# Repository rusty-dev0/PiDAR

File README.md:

# PiDAR
An autonomous robot that builds a real-time 2D map of an unknown room using LiDAR and SLAM, with live visualization and path tracking, and even a custom development board for all of its locomotive needs!

### Programming stuff:

The majority of the code here written for the kineticBoard would be written in the Pico C SDK. This is because abstraction, as seen with MicroPython, often causes delays and doesn't provide full control over the hardware. The Pi would be programmed in Python because it is better for data processing, visualizations, and (potentially) machine learning algorithms.

### A Little Context
I've always wanted to learn more about LiDARs and autonomous vehicles. This project will also serve as one of my projects for the online portion of the *Stasis* Hackathon, a Hack Club event.

## Organization and Flow
This project is basically divided into a few tiny subproblems that each component is designed to tackle. 
1) The LiDAR (at the top) is meant to collect data by sweeping the polar grid and recording ToF data when obstacles are detected (it knows this because its signal would bounce back). The LiDAR then feeds this real-time data to a Raspberry Pi 4 Model B.
2) The Pi, on the layer below, processes the data and allows for stuff like visualizations and algorithms. It's basically the brain of the robot. It takes an input from the layer above, processes it, and then handles an appropriate response such as sending a signal to the kineticBoard or responding to a request on its webserver.
3) The kineticBoard, at the very bottom, connects to the +12V LiPo and handles all of the low-level stuff with the motors. It connects to the encoders and reads the pulses generated by its fluctuating magnetic field, and also drives a response from its built-in TB6612FNG motor driver to the motor terminals themselves, allowing the robot to move forward, backward, spin, etc.

It's kind of like the OSI & TCP/IP model because the abstraction being lowered and lowered with every layer.

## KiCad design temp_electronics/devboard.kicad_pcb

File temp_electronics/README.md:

Stasis won't let me submit KiCAD stuff in a diff repo even though its linked as a submodule so I'm making a temporary copy here, but please check the actual submodule itself.

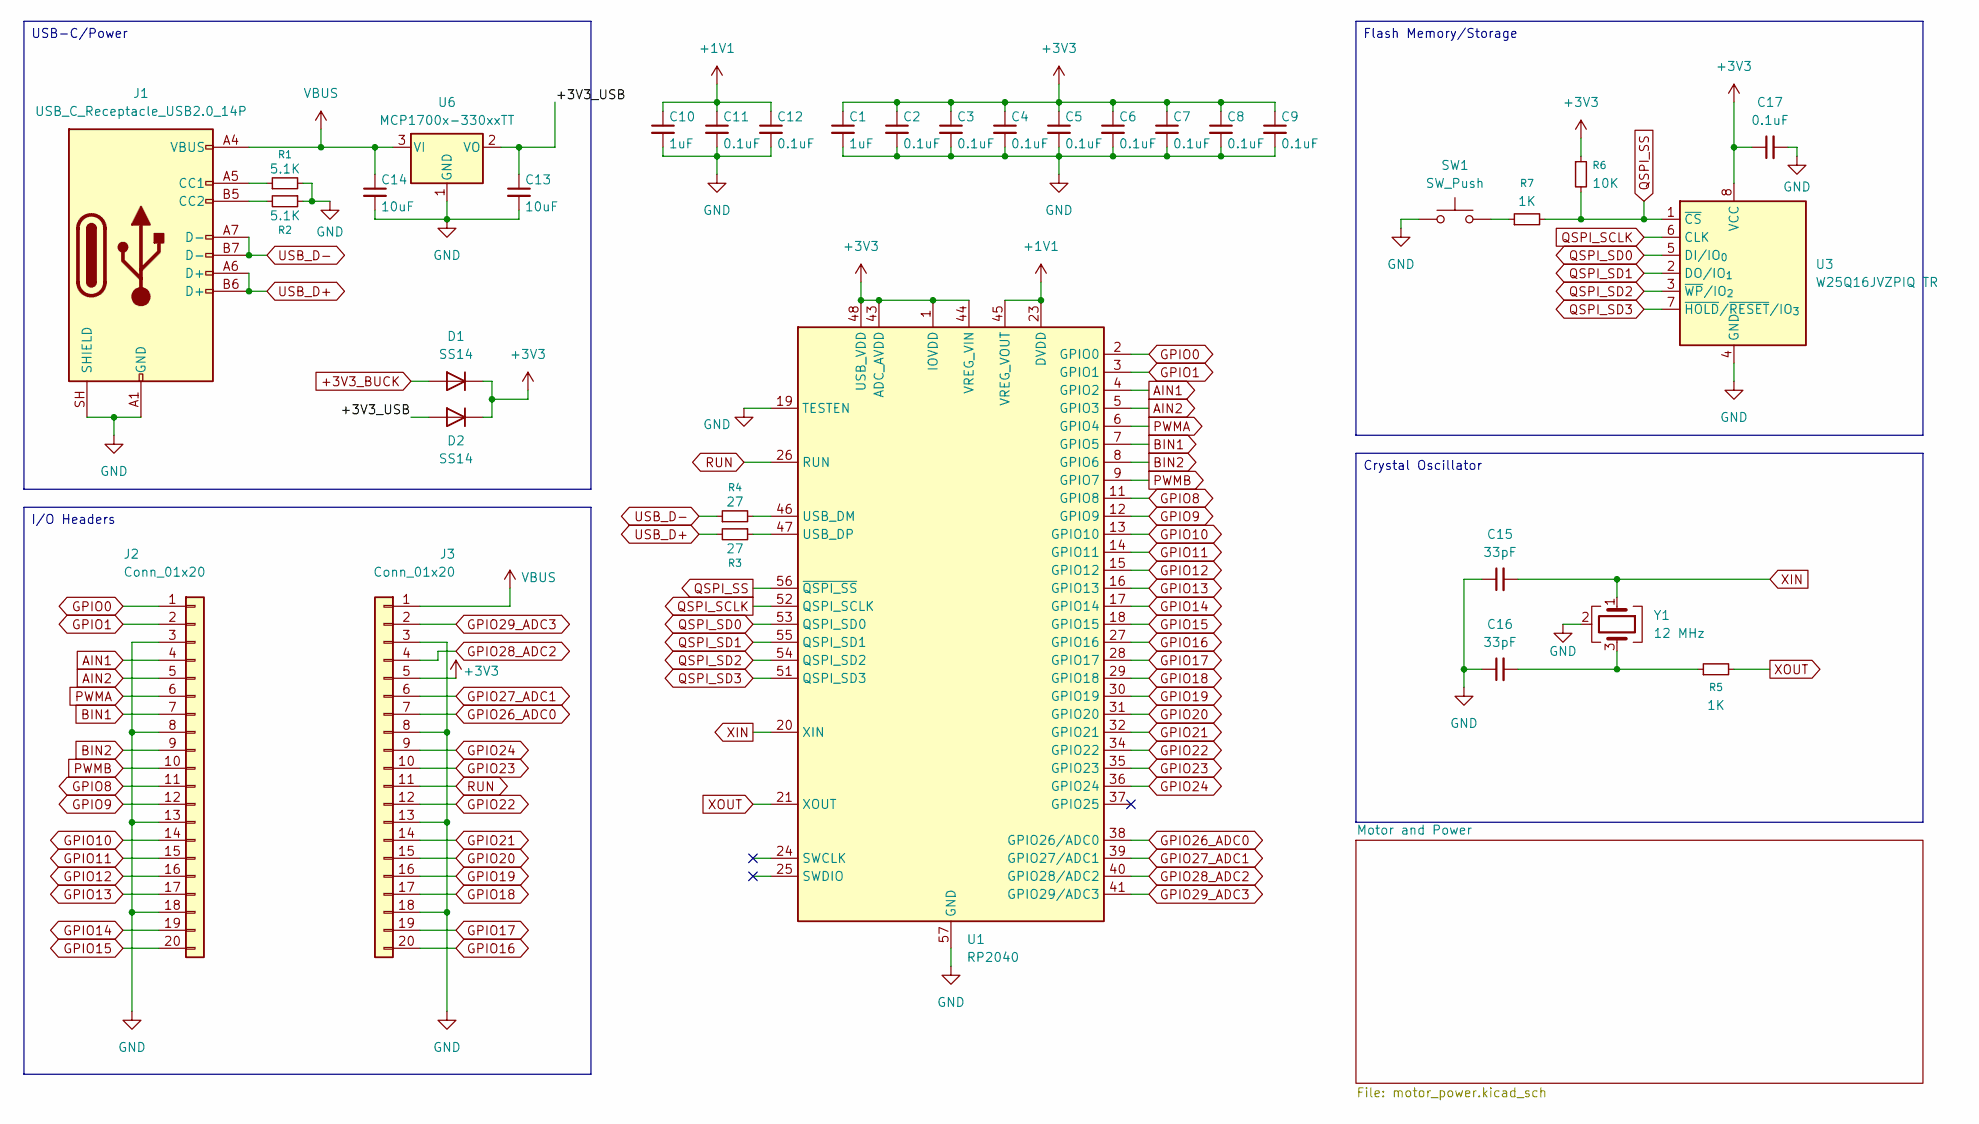
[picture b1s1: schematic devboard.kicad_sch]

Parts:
C1, C10: 1uF; C_0402_1005Metric
C2, C3, C4, C5, C6, C7, C8, C9, C11, C12, C17: 0.1uF; C_0402_1005Metric
C13, C14: 10uF; C_0603_1608Metric
C15, C16: 33pF; C_0402_1005Metric
D1, D2: SS14; D_SMA
J1: USB_C_Receptacle_USB2.0_14P; USB_C_Receptacle_HRO_TYPE-C-31-M-12
J2, J3: Conn_01x20; PinHeader_1x20_P2.54mm_Vertical
R1, R2: 5.1K; R_0402_1005Metric
R3, R4: 27; R_0402_1005Metric
R5, R7: 1K; R_0402_1005Metric
R6: 10K; R_0402_1005Metric
SW1: SW_Push; SW_Push_SPST_NO_Alps_SKRK
U1: RP2040; QFN-56-1EP_7x7mm_P0.4mm_EP3.2x3.2mm
U3: W25Q16JVZPIQ TR; Winbond_USON-8-1EP_3x2mm_P0.5mm_EP0.2x1.6mm
U6: MCP1700x-330xxTT; SOT-23
Y1: 12 MHz; Crystal_SMD_3225-4Pin_3.2x2.5mm

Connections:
+1V1: C10.1, C11.1, C12.1, U1.23 (DVDD), U1.45 (VREG_VOUT), U1.50 (DVDD)
+3V3: C1.1, C2.1, C3.1, C4.1, C5.1, C6.1, C7.1, C8.1, C9.1, C17.1, D1.1 (K), D2.1 (K), J3.5, R6.1, U1.1 (IOVDD), U1.10 (IOVDD), U1.22 (IOVDD), U1.33 (IOVDD), U1.42 (IOVDD), U1.43 (ADC_AVDD), U1.44 (VREG_VIN), U1.48 (USB_VDD), U1.49 (IOVDD), U3.8 (VCC); also elsewhere on the board
+3V3_BUCK: D1.2 (A); also elsewhere on the board
/+3V3_USB: C13.1, D2.2 (A), U6.2 (VO)
AIN1: J2.4, U1.4 (GPIO2); also elsewhere on the board
AIN2: J2.5, U1.5 (GPIO3); also elsewhere on the board
BIN1: J2.7, U1.7 (GPIO5); also elsewhere on the board
BIN2: J2.9, U1.8 (GPIO6); also elsewhere on the board
GND: C1.2, C2.2, C3.2, C4.2, C5.2, C6.2, C7.2, C8.2, C9.2, C10.2, C11.2, C12.2, C13.2, C14.2, C15.1, C16.1, C17.2, J1.A1 (GND), J1.A12 (GND), J1.B1 (GND), J1.B12 (GND), J1.SH (SHIELD), J2.3, J2.8, J2.13, J2.18, J3.3, J3.8, J3.13, J3.18, R1.2, R2.1, SW1.1, U1.19 (TESTEN), U1.57 (GND), U3.4 (GND), U6.1 (GND), Y1.2 (G), Y1.4 (G); also elsewhere on the board
GPIO0: J2.1, U1.2 (GPIO0)
GPIO1: J2.2, U1.3 (GPIO1)
GPIO8: J2.11, U1.11 (GPIO8)
GPIO9: J2.12, U1.12 (GPIO9)
GPIO10: J2.14, U1.13 (GPIO10)
GPIO11: J2.15, U1.14 (GPIO11)
GPIO12: J2.16, U1.15 (GPIO12)
GPIO13: J2.17, U1.16 (GPIO13)
GPIO14: J2.19, U1.17 (GPIO14)
GPIO15: J2.20, U1.18 (GPIO15)
GPIO16: J3.20, U1.27 (GPIO16)
GPIO17: J3.19, U1.28 (GPIO17)
GPIO18: J3.17, U1.29 (GPIO18)
GPIO19: J3.16, U1.30 (GPIO19)
GPIO20: J3.15, U1.31 (GPIO20)
GPIO21: J3.14, U1.32 (GPIO21)
GPIO22: J3.12, U1.34 (GPIO22)
GPIO23: J3.10, U1.35 (GPIO23)
GPIO24: J3.9, U1.36 (GPIO24)
GPIO26_ADC0: J3.7, U1.38 (GPIO26/ADC0)
GPIO27_ADC1: J3.6, U1.39 (GPIO27/ADC1)
GPIO28_ADC2: J3.4, U1.40 (GPIO28/ADC2)
GPIO29_ADC3: J3.2, U1.41 (GPIO29/ADC3)
unnamed: C16.2, R5.1, Y1.3
unnamed: J1.A5 (CC1), R1.1
unnamed: J1.B5 (CC2), R2.2
unnamed: R7.1, SW1.2
unnamed: R4.2, U1.46 (USB_DM)
unnamed: R3.1, U1.47 (USB_DP)
PWMA: J2.6, U1.6 (GPIO4); also elsewhere on the board
PWMB: J2.10, U1.9 (GPIO7); also elsewhere on the board
QSPI_SCLK: U1.52 (QSPI_SCLK), U3.6 (CLK)
QSPI_SD0: U1.53 (QSPI_SD0), U3.5 (DI/IO_{0})
QSPI_SD1: U1.55 (QSPI_SD1), U3.2 (DO/IO_{1})
QSPI_SD2: U1.54 (QSPI_SD2), U3.3 (~WP/IO_{2})
QSPI_SD3: U1.51 (QSPI_SD3), U3.7 (~HOLD/~RESET/IO_{3})
QSPI_SS: R6.2, R7.2, U1.56 (~QSPI_SS), U3.1 (~CS)
RUN: J3.11, U1.26 (RUN)
USB_D+: J1.A6 (D+), J1.B6 (D+), R3.2
USB_D-: J1.A7 (D-), J1.B7 (D-), R4.1
VBUS: C14.1, J1.A4 (VBUS), J1.A9 (VBUS), J1.B4 (VBUS), J1.B9 (VBUS), J3.1, U6.3 (VI)
XIN: C15.2, U1.20 (XIN), Y1.1
XOUT: R5.2, U1.21 (XOUT)

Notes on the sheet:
Crystal Oscillator
USB-C/Power
Flash Memory/Storage
I/O Headers

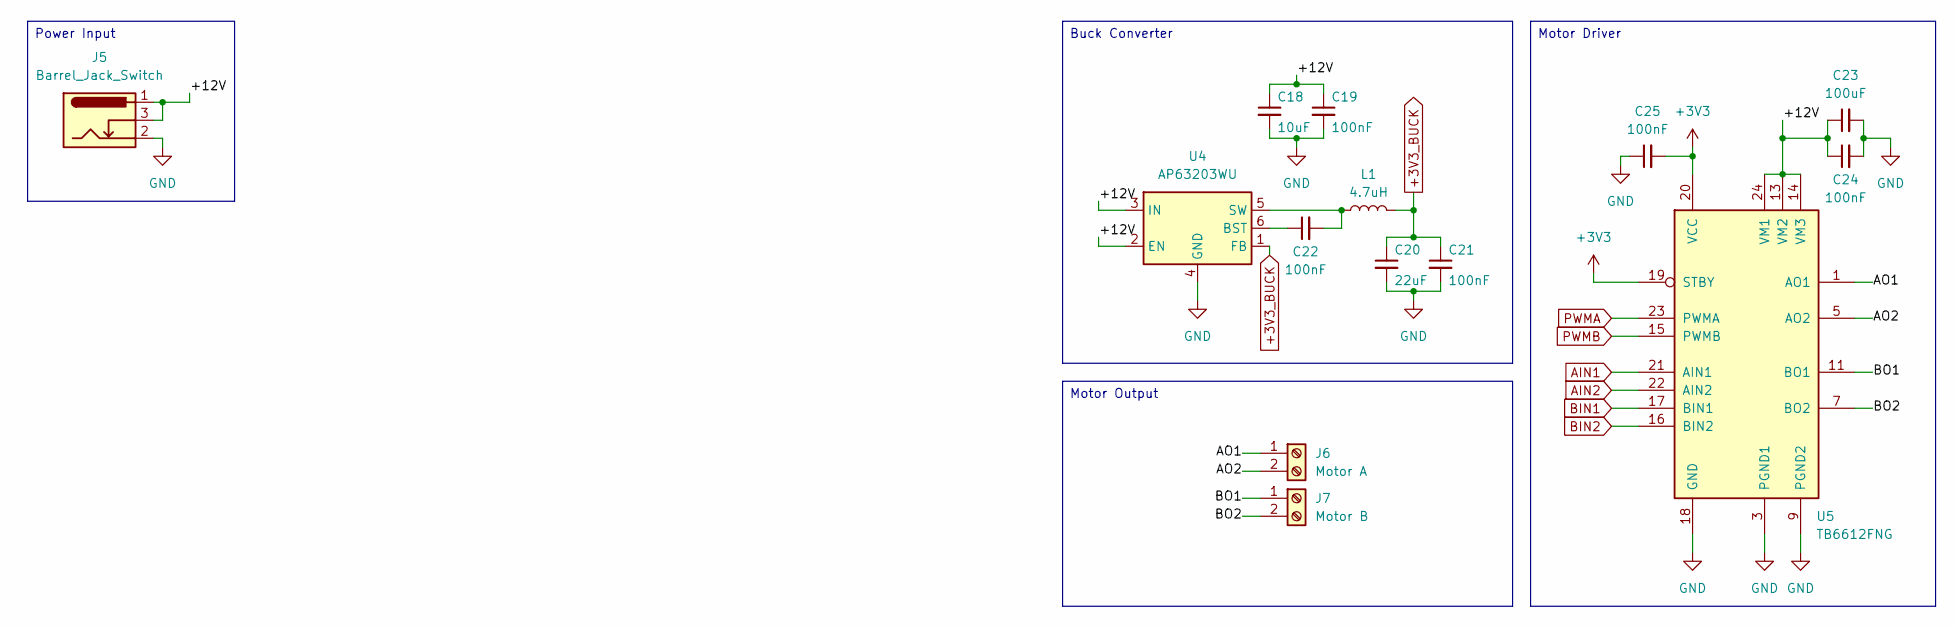
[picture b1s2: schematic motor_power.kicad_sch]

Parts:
C18: 10uF; C_0603_1608Metric
C19, C21, C22, C24, C25: 100nF; C_0402_1005Metric
C20: 22uF; C_0805_2012Metric
C23: 100uF; C_1206_3216Metric
J5: Barrel_Jack_Switch; BarrelJack_CUI_PJ-102AH_Horizontal
J6: Motor A; TerminalBlock_MaiXu_MX126-5.0-02P_1x02_P5.00mm
J7: Motor B; TerminalBlock_MaiXu_MX126-5.0-02P_1x02_P5.00mm
L1: 4.7uH; L_0805_2012Metric
U4: AP63203WU; TSOT-23-6
U5: TB6612FNG; SSOP-24_5.3x8.2mm_P0.65mm

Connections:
+3V3: C25.2, U5.19 (STBY), U5.20 (VCC); also elsewhere on the board
+3V3_BUCK: C20.1, C21.1, L1.2, U4.1 (FB); also elsewhere on the board
/Motor and Power/+12V: C18.1, C19.1, C23.1, C24.1, J5.1, J5.3, U4.2 (EN), U4.3 (IN), U5.13 (VM2), U5.14 (VM3), U5.24 (VM1)
/Motor and Power/AO1: J6.1, U5.1 (AO1), U5.2 (AO1)
/Motor and Power/AO2: J6.2, U5.5 (AO2), U5.6 (AO2)
/Motor and Power/BO1: J7.1, U5.11 (BO1), U5.12 (BO1)
/Motor and Power/BO2: J7.2, U5.7 (BO2), U5.8 (BO2)
AIN1: U5.21 (AIN1); also elsewhere on the board
AIN2: U5.22 (AIN2); also elsewhere on the board
BIN1: U5.17 (BIN1); also elsewhere on the board
BIN2: U5.16 (BIN2); also elsewhere on the board
GND: C18.2, C19.2, C20.2, C21.2, C23.2, C24.2, C25.1, J5.2, U4.4 (GND), U5.3 (PGND1), U5.4 (PGND1), U5.9 (PGND2), U5.10 (PGND2), U5.18 (GND); also elsewhere on the board
unnamed: C22.1, U4.6 (BST)
unnamed: C22.2, L1.1, U4.5 (SW)
PWMA: U5.23 (PWMA); also elsewhere on the board
PWMB: U5.15 (PWMB); also elsewhere on the board

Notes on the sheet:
Motor Output
Power Input
Buck Converter
Motor Driver

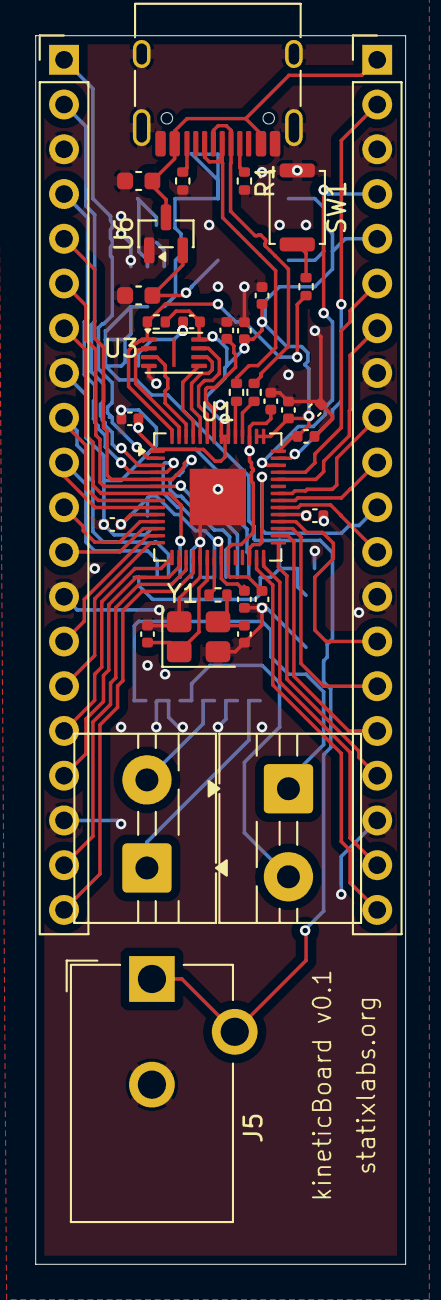
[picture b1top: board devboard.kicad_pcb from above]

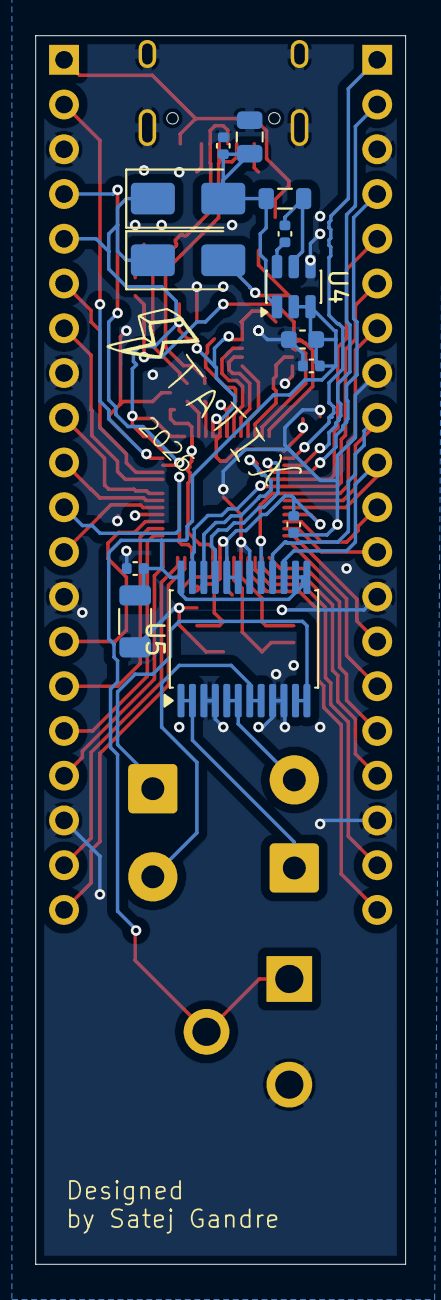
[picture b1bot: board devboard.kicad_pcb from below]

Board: 4 copper layers, 21.0 x 69.8 mm, 48 parts (13 on the bottom side), 59 nets.

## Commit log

2026-04-02 added lower portion of the robot chasis
2026-04-02 sketched out a diagram in Lucid and updated readme
2026-04-04 finished chasis design (hopefully)
2026-04-04 finished chasis f3d
2026-04-04 added step variants of finished chasis plates
2026-04-04 added files back??
2026-04-19 added the kineticBoard as a submodule
2026-04-21 updated kinetic board
2026-04-22 pcb update
2026-05-02 updated to the finished board
2026-05-03 completed assembly
2026-05-03 reorganized directories
2026-05-03 added basic firmware for the tb6612fng
2026-05-04 added debug
2026-05-04 added BOM
2026-05-04 copied submodule content in current repo to pass stasis autochecks
2026-05-07 added images of kineticBoard
2026-06-26 stasis journal
